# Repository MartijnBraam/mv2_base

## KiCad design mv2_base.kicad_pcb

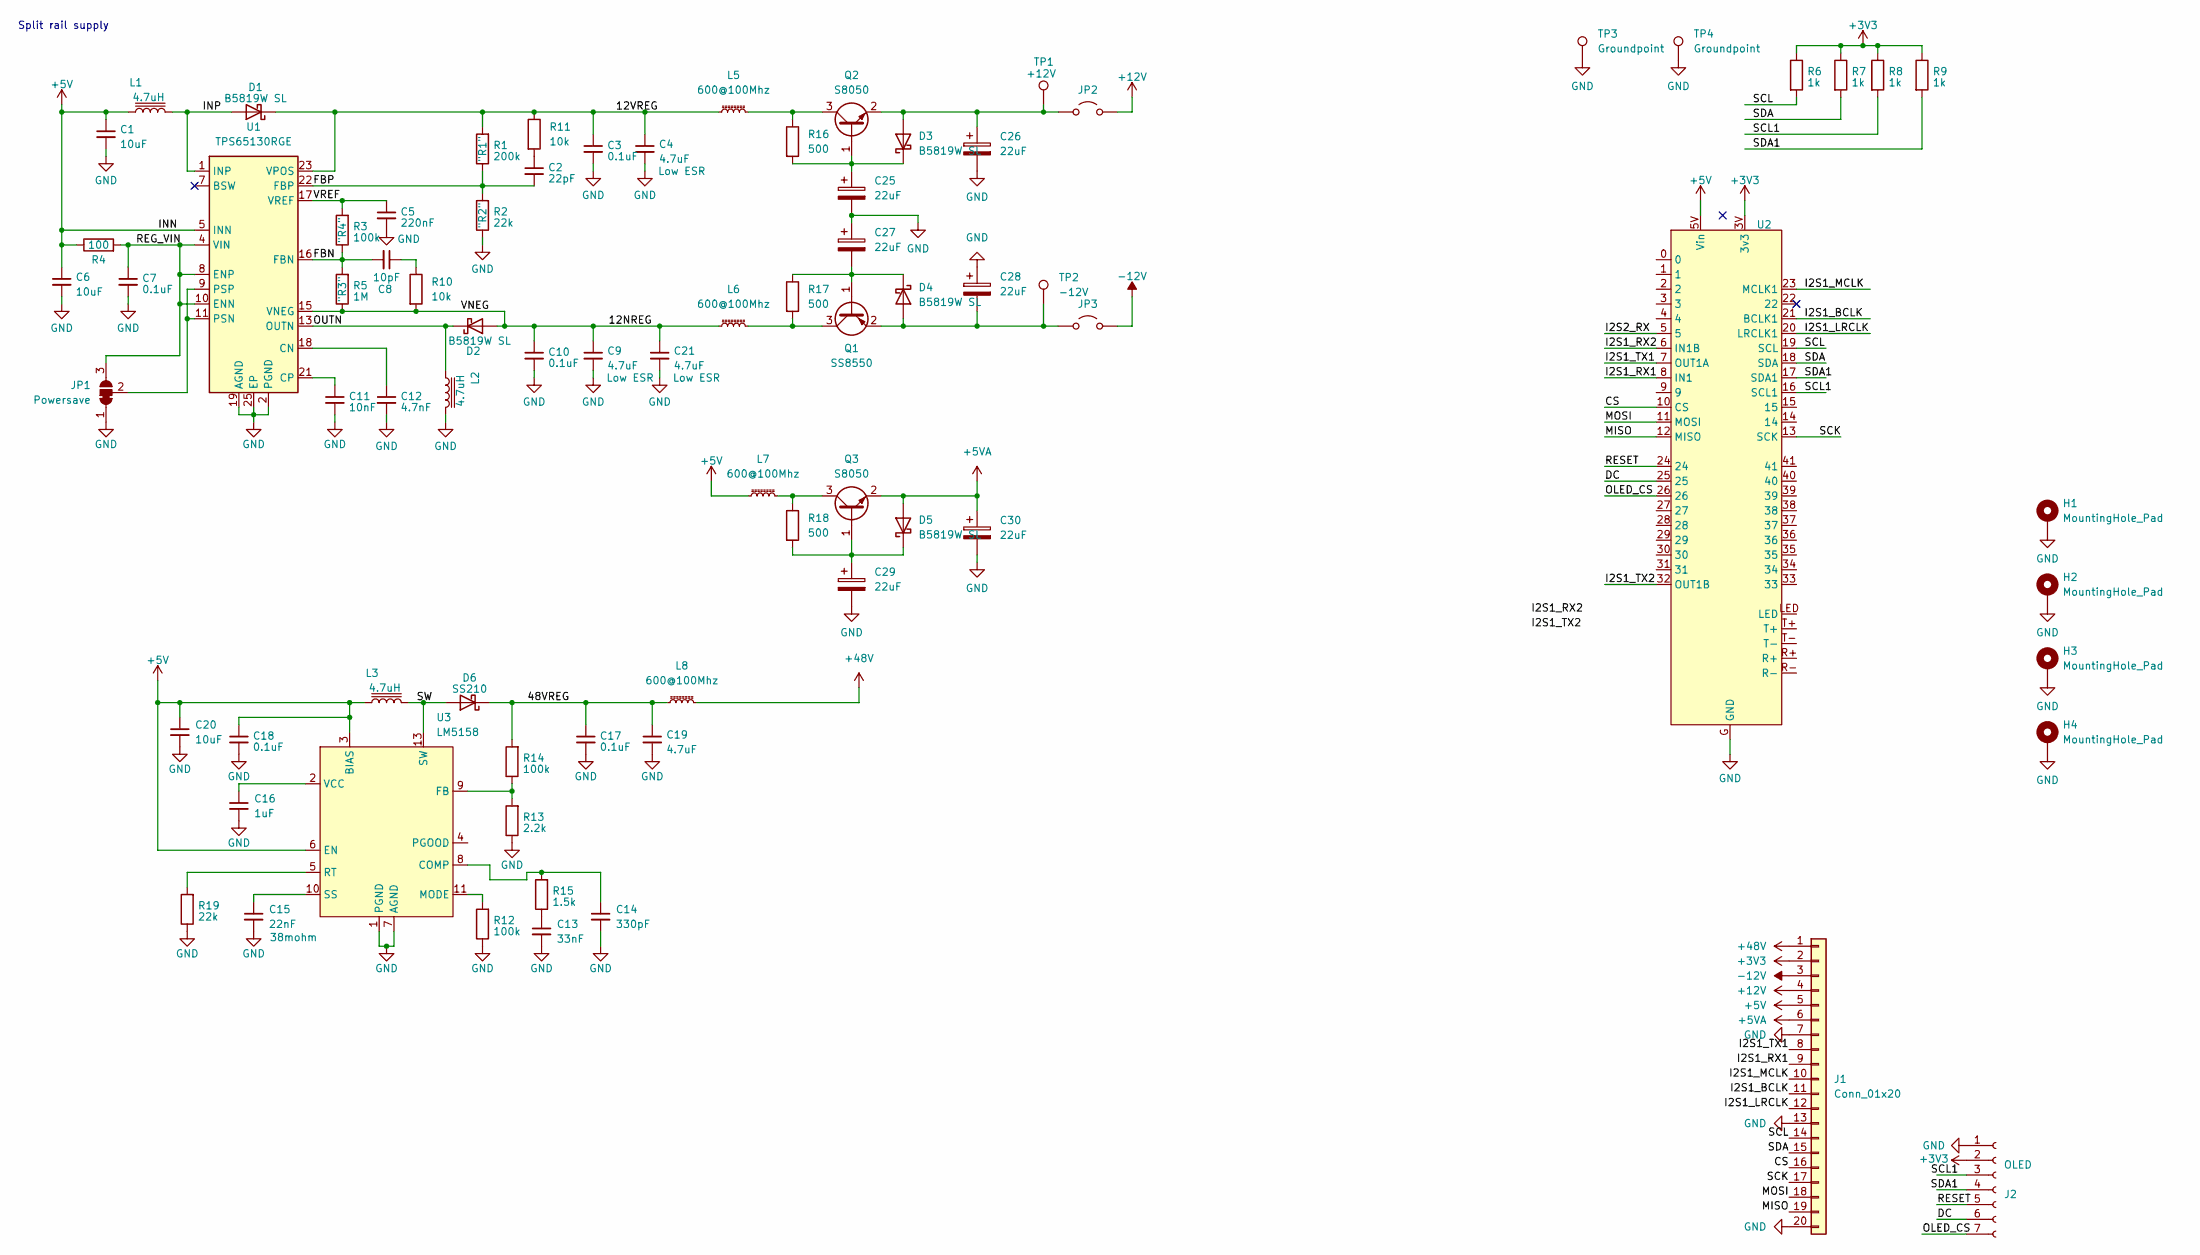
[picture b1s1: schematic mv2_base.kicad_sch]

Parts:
C1, C20: 10uF; C_0805_2012Metric_Pad1.18x1.45mm_HandSolder; LCSC C15850
C2: 22pF; C_0402_1005Metric; LCSC C1555
C3: 0.1uF; C_0603_1608Metric_Pad1.08x0.95mm_HandSolder; LCSC C14663
C4: 4.7uF; C_0805_2012Metric_Pad1.18x1.45mm_HandSolder; LCSC C1779
C5: 220nF; C_0402_1005Metric; LCSC C16772
C6: 10uF; C_0805_2012Metric; LCSC C15850
C7, C10, C17, C18: 0.1uF; C_0402_1005Metric; LCSC C307331
C8: 10pF; C_0402_1005Metric; LCSC C32949
C9, C19, C21: 4.7uF; C_0805_2012Metric; LCSC C1779
C11: 10nF; C_0402_1005Metric; LCSC C15195
C12: 4.7nF; C_0402_1005Metric; LCSC C1538
C13: 33nF; C_0603_1608Metric; LCSC C21117
C14: 330pF; C_0603_1608Metric; LCSC C1664
C15: 22nF; C_0402_1005Metric; LCSC C1532
C16: 1uF; C_0402_1005Metric; LCSC C52923
C25, C26, C27, C28, C29, C30: 22uF; C_0805_2012Metric; LCSC C45783
D1, D2, D3, D4, D5: B5819W SL; D_SOD-123; LCSC C8598
D6: SS210; D_SMA; LCSC C14996
H1, H2, H3, H4: MountingHole_Pad; MountingHole_3.2mm_M3_Pad_Via
J1: Conn_01x20; PinHeader_1x20_P2.54mm_Vertical
J2: OLED; PinHeader_1x07_P2.54mm_Vertical
JP1: Powersave; SolderJumper-3_P1.3mm_Bridged2Bar12_Pad1.0x1.5mm_NumberLabe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
JP2, JP3: Jumper_2_Open; PinHeader_1x02_P2.54mm_Vertical
L1, L2, L3: 4.7uH; L_Wuerth_WE-TPC-3816; MPN 744031004
L5, L6, L7, L8: 600@100Mhz; L_0603_1608Metric; LCSC C1002
Q1: SS8550; SOT-23; LCSC C8542
Q2, Q3: S8050; SOT-23; LCSC C2146
R1: 200k; R_0402_1005Metric; LCSC C25764
R2, R19: 22k; R_0402_1005Metric; LCSC C25768
R3, R12, R14: 100k; R_0402_1005Metric; LCSC C25741
R4: 100; R_0402_1005Metric; LCSC C25076
R5: 1M; R_0402_1005Metric; LCSC C26083
R6, R7, R8, R9: 1k; R_0603_1608Metric_Pad0.98x0.95mm_HandSolder; LCSC C21190
R10, R11: 10k; R_0402_1005Metric
R13: 2.2k; R_0402_1005Metric; LCSC C25879
R15: 1.5k; R_0402_1005Metric; LCSC C25867
R16, R17, R18: 500; R_0402_1005Metric
TP1: +12V; TestPoint_Plated_Hole_D2.0mm
TP2: -12V; TestPoint_Plated_Hole_D2.0mm
TP3, TP4: Groundpoint; TestPoint_Bridge_Pitch2.54mm_Drill1.0mm
U1: TPS65130RGE; VQFN-24-1EP_4x4mm_P0.5mm_EP2.45x2.45mm_ThermalVias; LCSC C54989
U2: Teensy41
U3: LM5158; WQFN-16-1EP_3x3mm_P0.5mm_EP1.68x1.68mm_ThermalVias

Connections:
+3V3: J1.2, J2.2, R6.1, R7.1, R8.1, R9.1, U2.3V (3v3)
+5V: C1.1, C6.1, C18.1, C20.1, J1.5, L1.2, L3.2, L7.1, R4.1, U1.5 (INN), U1.6 (INN), U2.5V (Vin), U3.3 (BIAS), U3.6 (EN)
+5VA: C30.1, D5.2 (A), J1.6, Q3.2 (E)
+12V: J1.4, JP2.2 (B)
+48V: J1.1, L8.2
-12V: J1.3, JP3.2 (B)
/12NREG: C9.1, C10.1, C21.1, D2.2 (A), L6.1, R5.1, R10.2, U1.15 (VNEG)
/12VREG: C3.1, C4.1, D1.1 (K), L5.1, R1.2, R11.1, U1.23 (VPOS)
/48VREG: C17.1, C19.1, D6.1 (K), L8.1, R14.2
/CS: J1.16, U2.10 (CS)
/DC: J2.6, U2.25
/FBN: C8.2, R3.1, R5.2, U1.16 (FBN)
/FBP: C2.2, R1.1, R2.2, U1.22 (FBP)
/I2S1_BCLK: J1.11, U2.21 (BCLK1)
/I2S1_LRCLK: J1.12, U2.20 (LRCLK1)
/I2S1_MCLK: J1.10, U2.23 (MCLK1)
/I2S1_RX1: J1.9, U2.8 (IN1)
/I2S1_RX2: U2.6 (IN1B)
/I2S1_TX1: J1.8, U2.7 (OUT1A)
/I2S1_TX2: U2.32 (OUT1B)
/I2S2_RX: U2.5
/INP: D1.2 (A), L1.1, U1.1 (INP), U1.24 (INP)
/MISO: J1.19, U2.12 (MISO)
/MOSI: J1.18, U2.11 (MOSI)
/OLED_CS: J2.7, U2.26
/OUTN: D2.1 (K), L2.2, U1.13 (OUTN), U1.14 (OUTN)
/REG_VIN: C7.1, JP1.3 (B), R4.2, U1.4 (VIN), U1.8 (ENP), U1.10 (ENN)
/RESET: J2.5, U2.24
/SCK: J1.17, U2.13 (SCK)
/SCL: J1.14, R6.2, U2.19 (SCL)
/SCL1: J2.3, R8.2, U2.16 (SCL1)
/SDA: J1.15, R7.2, U2.18 (SDA)
/SDA1: J2.4, R9.2, U2.17 (SDA1)
/SW: D6.2 (A), L3.1, U3.13 (SW), U3.14 (SW)
/VREF: C5.1, R3.2, U1.17 (VREF)
GND: C1.2, C3.2, C4.2, C5.2, C6.2, C7.2, C9.2, C10.2, C11.2, C12.2, C13.2, C14.2, C15.2, C16.2, C17.2, C18.2, C19.2, C20.2, C21.2, C25.2, C26.2, C27.1, C28.1, C29.2, C30.2, H1.1, H2.1, H3.1, H4.1, J1.7, J1.13, J1.20, J2.1, JP1.1 (A), L2.1, R2.1, R12.1, R13.1, R19.1, TP3.1, TP4.1, U1.2 (PGND), U1.3 (PGND), U1.19 (AGND), U1.25 (EP), U2.G (GND), U3.1 (PGND), U3.7 (AGND), U3.16 (PGND)
unnamed: C2.1, R11.2
unnamed: C8.1, R10.1
unnamed: C13.1, R15.1
unnamed: C26.1, D3.2 (A), JP2.1 (A), Q2.2 (E), TP1.1
unnamed: C25.1, D3.1 (K), Q2.1 (B), R16.2
unnamed: C28.2, D4.2 (A), JP3.1 (A), Q1.2 (E), TP2.1
unnamed: C27.2, D4.1 (K), Q1.1 (B), R17.1
unnamed: C29.1, D5.1 (K), Q3.1 (B), R18.2
unnamed: JP1.2 (C), U1.9 (PSP), U1.11 (PSN)
unnamed: L6.2, Q1.3 (C), R17.2
unnamed: L5.2, Q2.3 (C), R16.1
unnamed: L7.2, Q3.3 (C), R18.1
unnamed: C12.1, U1.18 (CN)
unnamed: C11.1, U1.21 (CP)
unnamed: C14.1, R15.2, U3.8 (COMP)
unnamed: R13.2, R14.1, U3.9 (FB)
unnamed: R12.2, U3.11 (MODE)
unnamed: R19.2, U3.5 (RT)
unnamed: C15.1, U3.10 (SS)
unnamed: C16.1, U3.2 (VCC)

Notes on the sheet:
Split rail supply

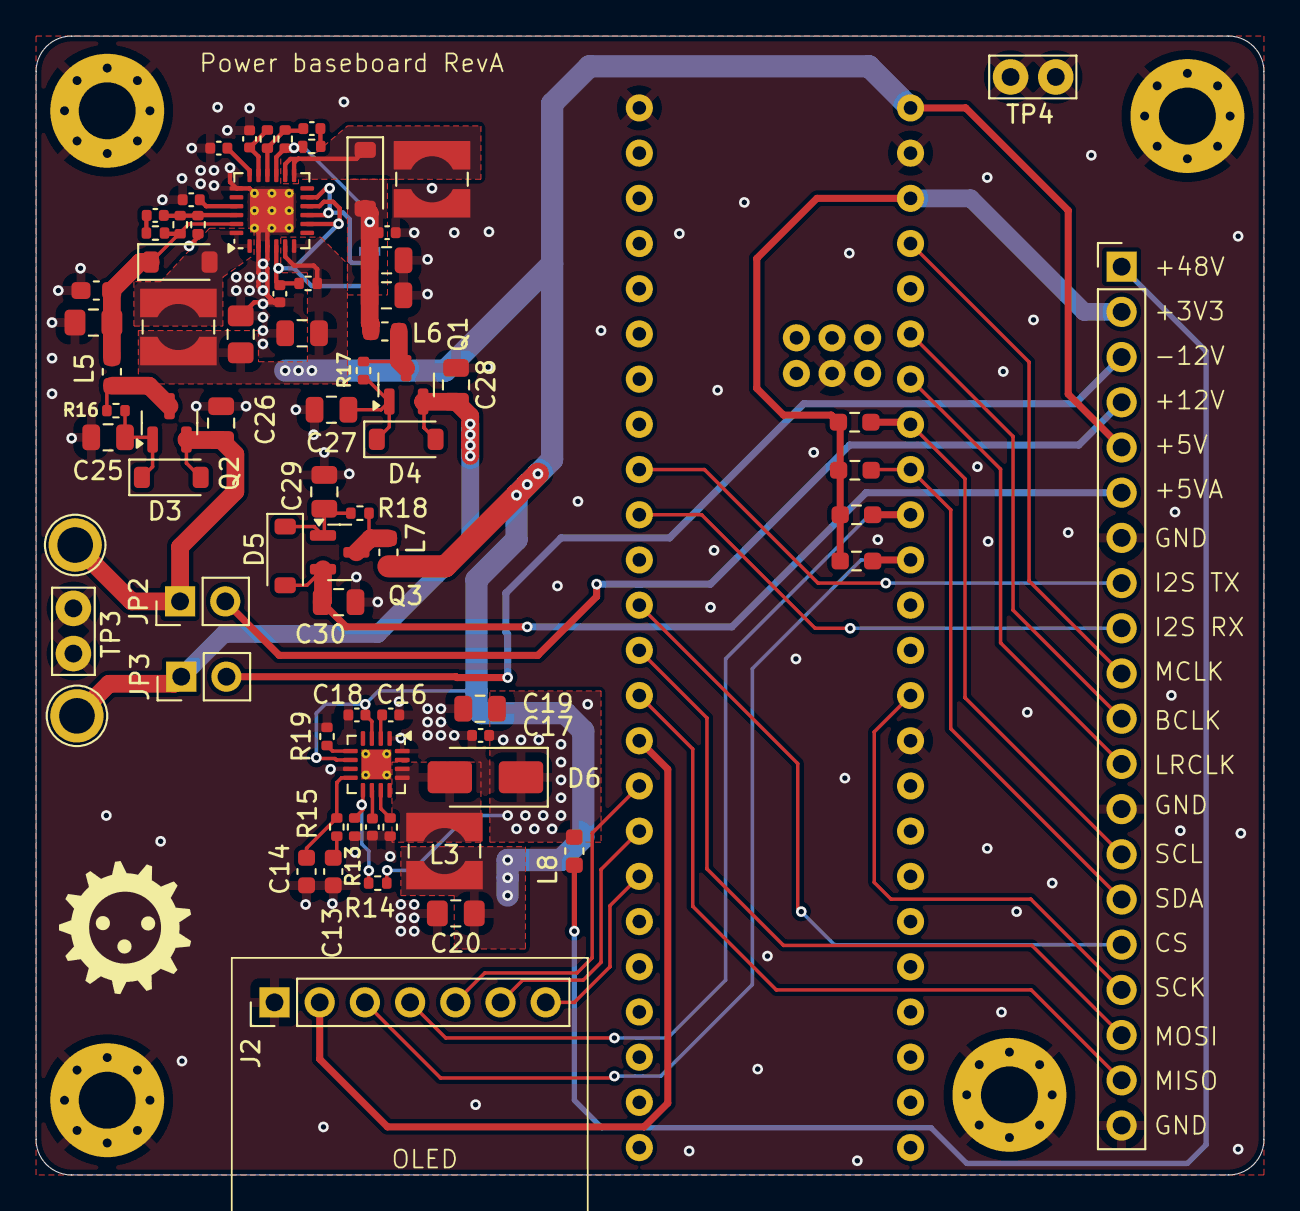
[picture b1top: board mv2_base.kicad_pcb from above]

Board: 4 copper layers, 69.0 x 64.0 mm, 78 parts (1 on the bottom side), 53 nets.

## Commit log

2025-02-07 Add jumpers in power rails and more test points
2025-03-23 Add gitattributes
2025-03-23 New filters
2025-03-24 Implement +48V supply
2025-06-11 Fix up some LCSC part numbers
2025-06-11 DRC fixes
2025-06-11 Replace 500ohm resistor with 510ohm basic part
